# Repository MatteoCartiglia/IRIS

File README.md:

# IRIS: Interface for Real time Intelligent Systems

##  Overview

IRIS contains the necessary resources to interface custom ASICS built in the NCS group with Teensy microcontroller boards. 
IRIS enables novel chips to be prototyped and tested quickly and efficiently without having to deal with tedious interfacing.  It interfaces seamlessly different communication protocols such as I2C, SPI and custom four phase handshakes. Doing so  different building blocks can be reconfigured to meet the demands of any new chip.

The building blocks it supports are:
- DAC
- Input interface
- SPI
- BiasGenerator
- Output Encoder

## Code overview

A user friendly GUI controls the backend which runs on the teensy board. Communication between these two parts is crucial and ensures accurate transmission of all data. 

## Frontend

The frontend runs using the 'Dear ImGui' (https://github.com/ocornut/imgui) C++ interface with GLFW (http://www.glfw.org) and OpenGL (https://www.opengl.org/) backends. The relevant files of ImGui and OpenGL are included in this repository. 

## Backend

This code is compiled and uploaded using "PlatformIO" plugin on Visual Studio Code.

## Getting Started

1. Install the required dependencies (GLFW, platformIO plugin)
2. Connect the Teensy to the PC and check how it appears in the /dev directory. You can do this by running `ls /dev`. It will typically appear as `ttyACM0`, however it may also appear under another name, depending on your machine. If it does not appear as `ttyACM0`, update the `SERIAl_PORT_NAME` variable in the `teensy_backend/include/constants.h` file.
3. Upload the backend code to Teensy using the PlatformIO plugin.
4. In the `imgui_frontend` directory, run the shell script `clean_build_ruh.sh`. This will build and run an `alive_interface` executable.

Current boards that have been tested are:
- ALIVE
- SPIAC
- AHPC

## Contributors:
* Matteo Cartiglia

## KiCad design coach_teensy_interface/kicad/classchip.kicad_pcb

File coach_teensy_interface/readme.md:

## Overview

This project contains the resources necessary to use a [Teensy 4.0](https://www.pjrc.com/store/teensy40.html) to interface with the CoACH neuromorphic classchip via the PLANE board.

The `datasheets` folder contains datasheets for the chips used on the PCB.

The `kicad` folder contains the schematic and layout of the PCB.

The `src/config` folder contains a file used by CMake to provide version number macros.

The `src/pc` folder contains code to build a Python extension module (`pyplane`) through which the PLANE board and CoACH chip can be controlled from Python.

The `src/teensy` folder contains the code that needs to be uploaded to the Teensy.

The CoACH chip itself is documented in the [CoACH-docs project](https://code.ini.uzh.ch/CoACH/CoACH-docs).

## To Build the Software

### Prerequisites
* Linux, preferably Ubuntu
* Arduino software
* Teensyduino
* `teensy_loader_cli` from https://github.com/PaulStoffregen/teensy_loader_cli - see comments in [load-teensy.sh](load-teensy.sh) for detailed build and install instructions
* pybind11: https://pybind11.readthedocs.io - see https://pybind11.readthedocs.io/en/stable/installing.html#include-with-pypi for installation instructions (Hint: you probably want to use the `pip install "pybind11[global]"` method in order to get the pybind11 CMake files, but this will depend on your environment)

The Arduino software and Teensyarduino can be installed as follows:

```
cd /parent/dir/for/arduino/software
wget https://downloads.arduino.cc/arduino-1.8.13-linux64.tar.xz
wget https://www.pjrc.com/teensy/td_153/TeensyduinoInstall.linux64
tar -xf arduino-1.8.13-linux64.tar.xz
chmod +x TeensyduinoInstall.linux64
./TeensyduinoInstall.linux64 --dir=arduino-1.8.13
cd arduino-1.8.13/hardware/teensy/avr/cores/teensy4
make main.elf
```

Once you have all the prerequisites installed, you can clone this project and proceed to build it as follows.

### Command Line Build

In the `CoACH_teensy_interface` directory, do the following (replacing `/parent/dir/for/arduino/software/arduino-1.8.13` with the actual directory you installed the Arduino software in, obviously).

```
mkdir build && cd build
cmake -DARDUINOPATH=/parent/dir/for/arduino/software/arduino-1.8.13 ../src
make -j
```

The build produces
* `teensy/main.hex` which can be uploaded to the Teensy using the `load-teensy.sh` script, which in turn uses `teensy_loader_cli`.
* The Python extension module e.g. `pc/pyplane/pyplane.cpython-36m-x86_64-linux-gnu.so` which needs to be on the `PYTHONPATH` in order to be importable from Python.

### Building the Teensy Code using an IDE

An IDE can be used to take care of compiling and uploading the code to the Teensy. For Visual Studio Code, the [PlatformIO](https://platformio.org/) extension can be used for this. To do this with the Arduino IDE, follow [these](https://www.pjrc.com/teensy/td_download.html) instructions.

If Visual Studio Code is to be used, create a new project from the PlatformIO home screen. Choose Teensy 4.0 as the board and Arduino as the framework. Then copy everything in `teensy/*` to the `src/*` folder of the newly created project.

If the Arduino IDE is to be used, rename `teensy/main.cpp` to `teensy/teensy.ino`.

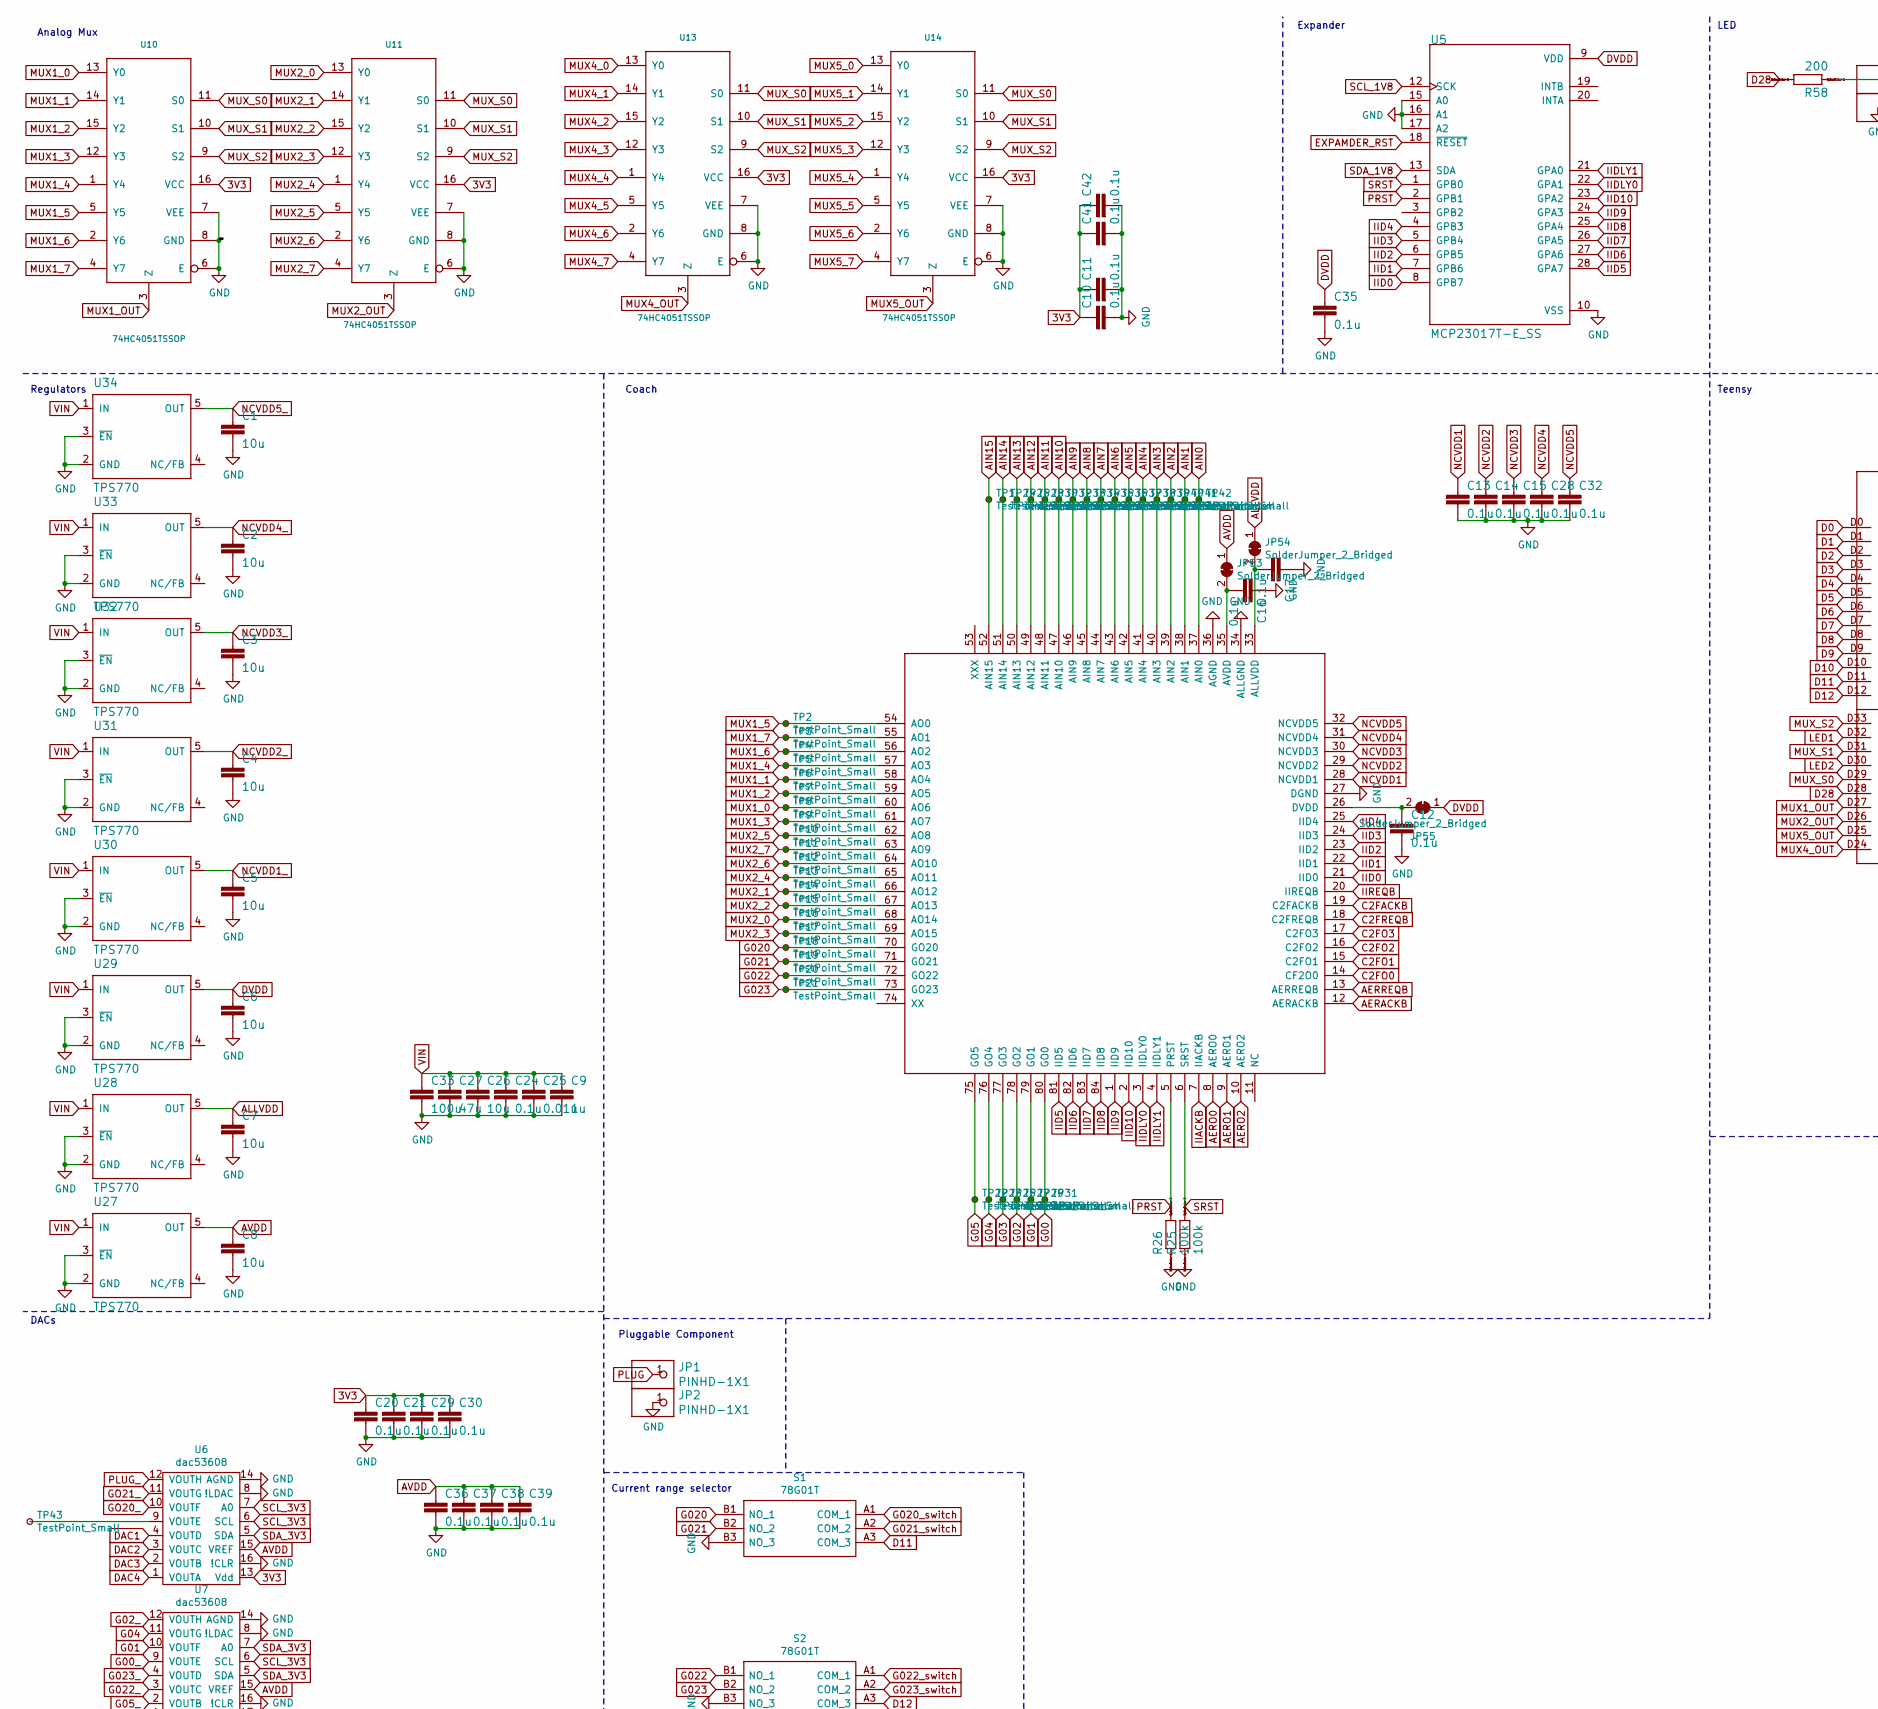
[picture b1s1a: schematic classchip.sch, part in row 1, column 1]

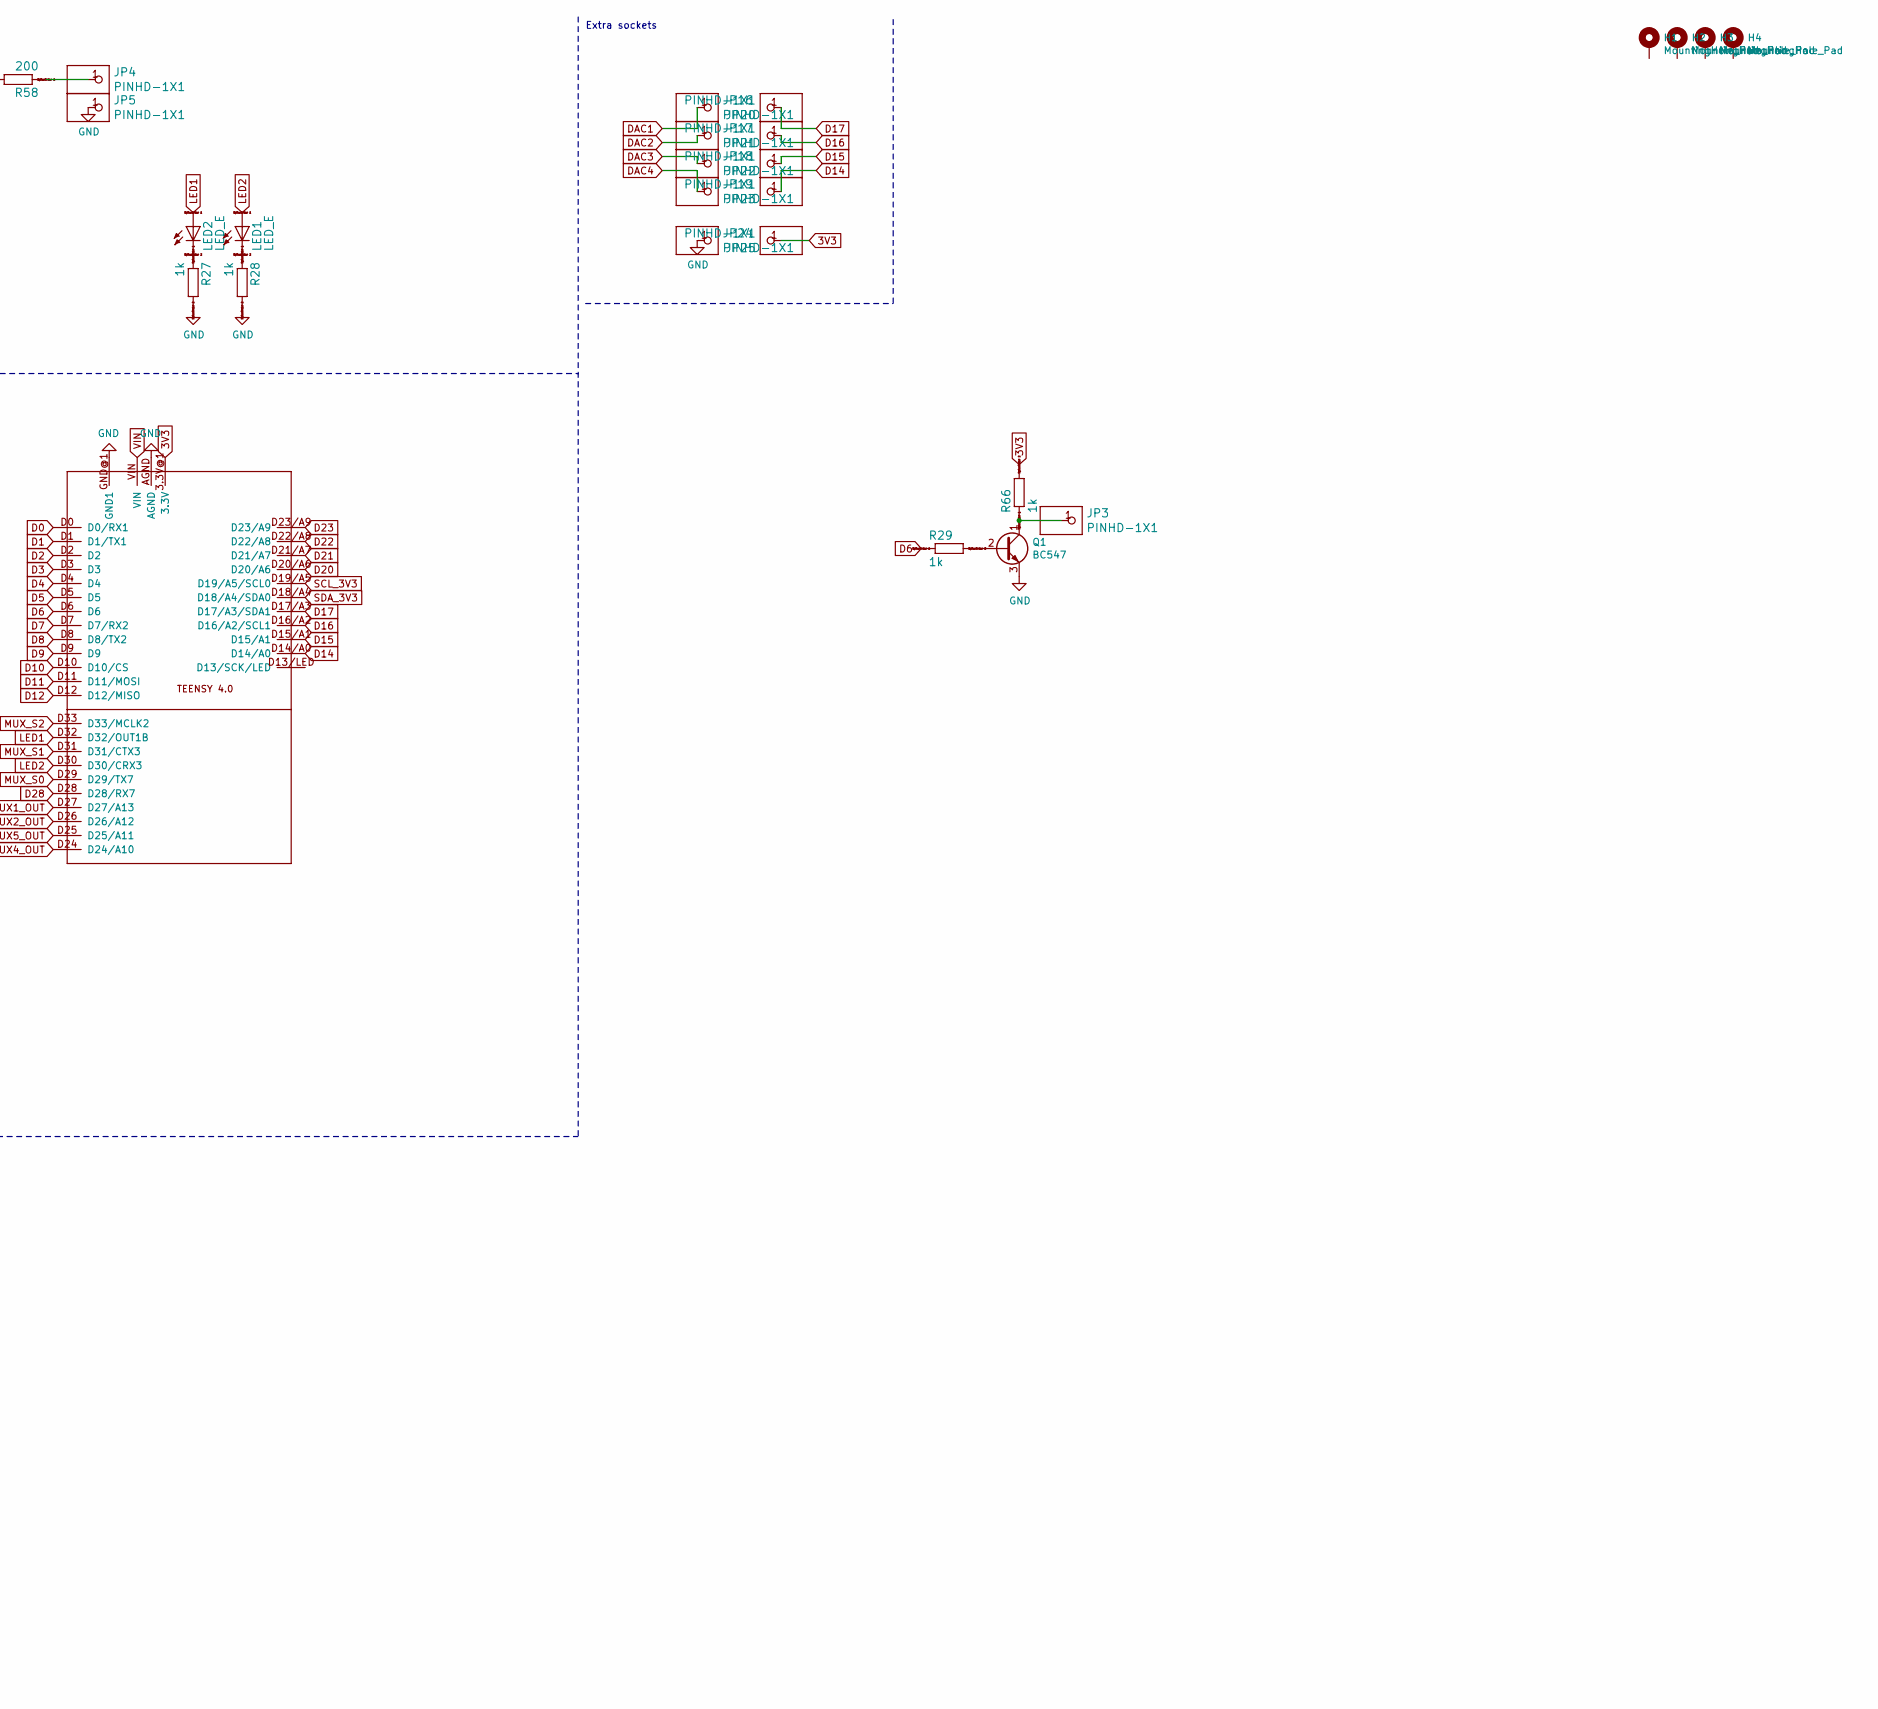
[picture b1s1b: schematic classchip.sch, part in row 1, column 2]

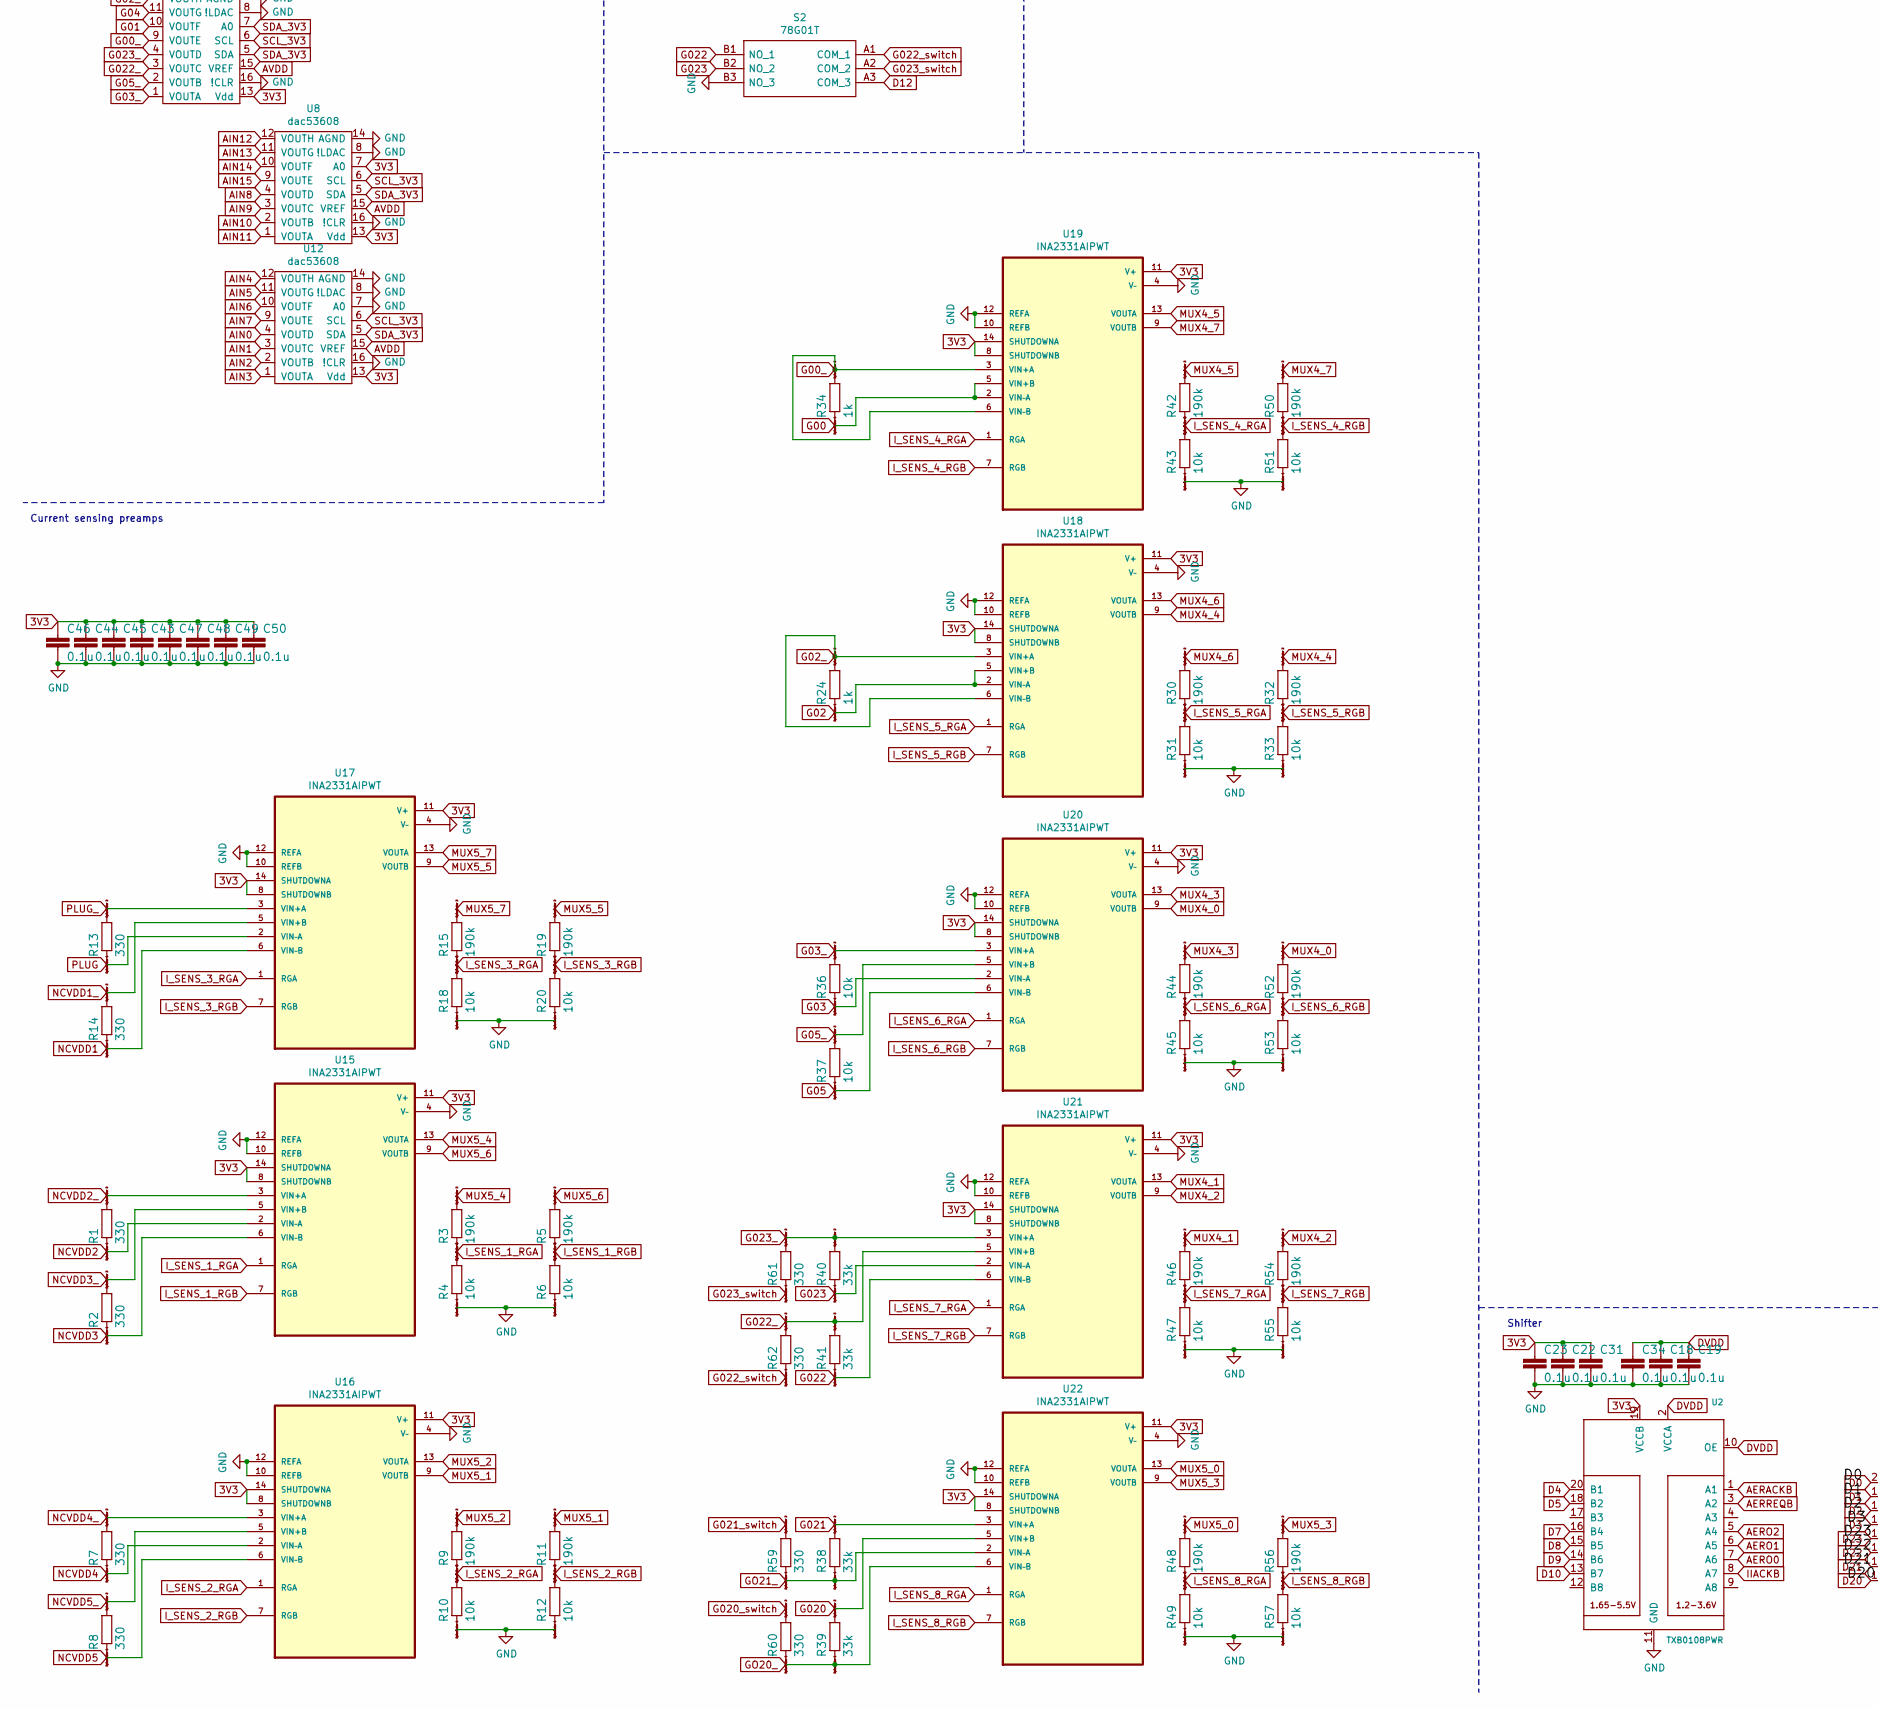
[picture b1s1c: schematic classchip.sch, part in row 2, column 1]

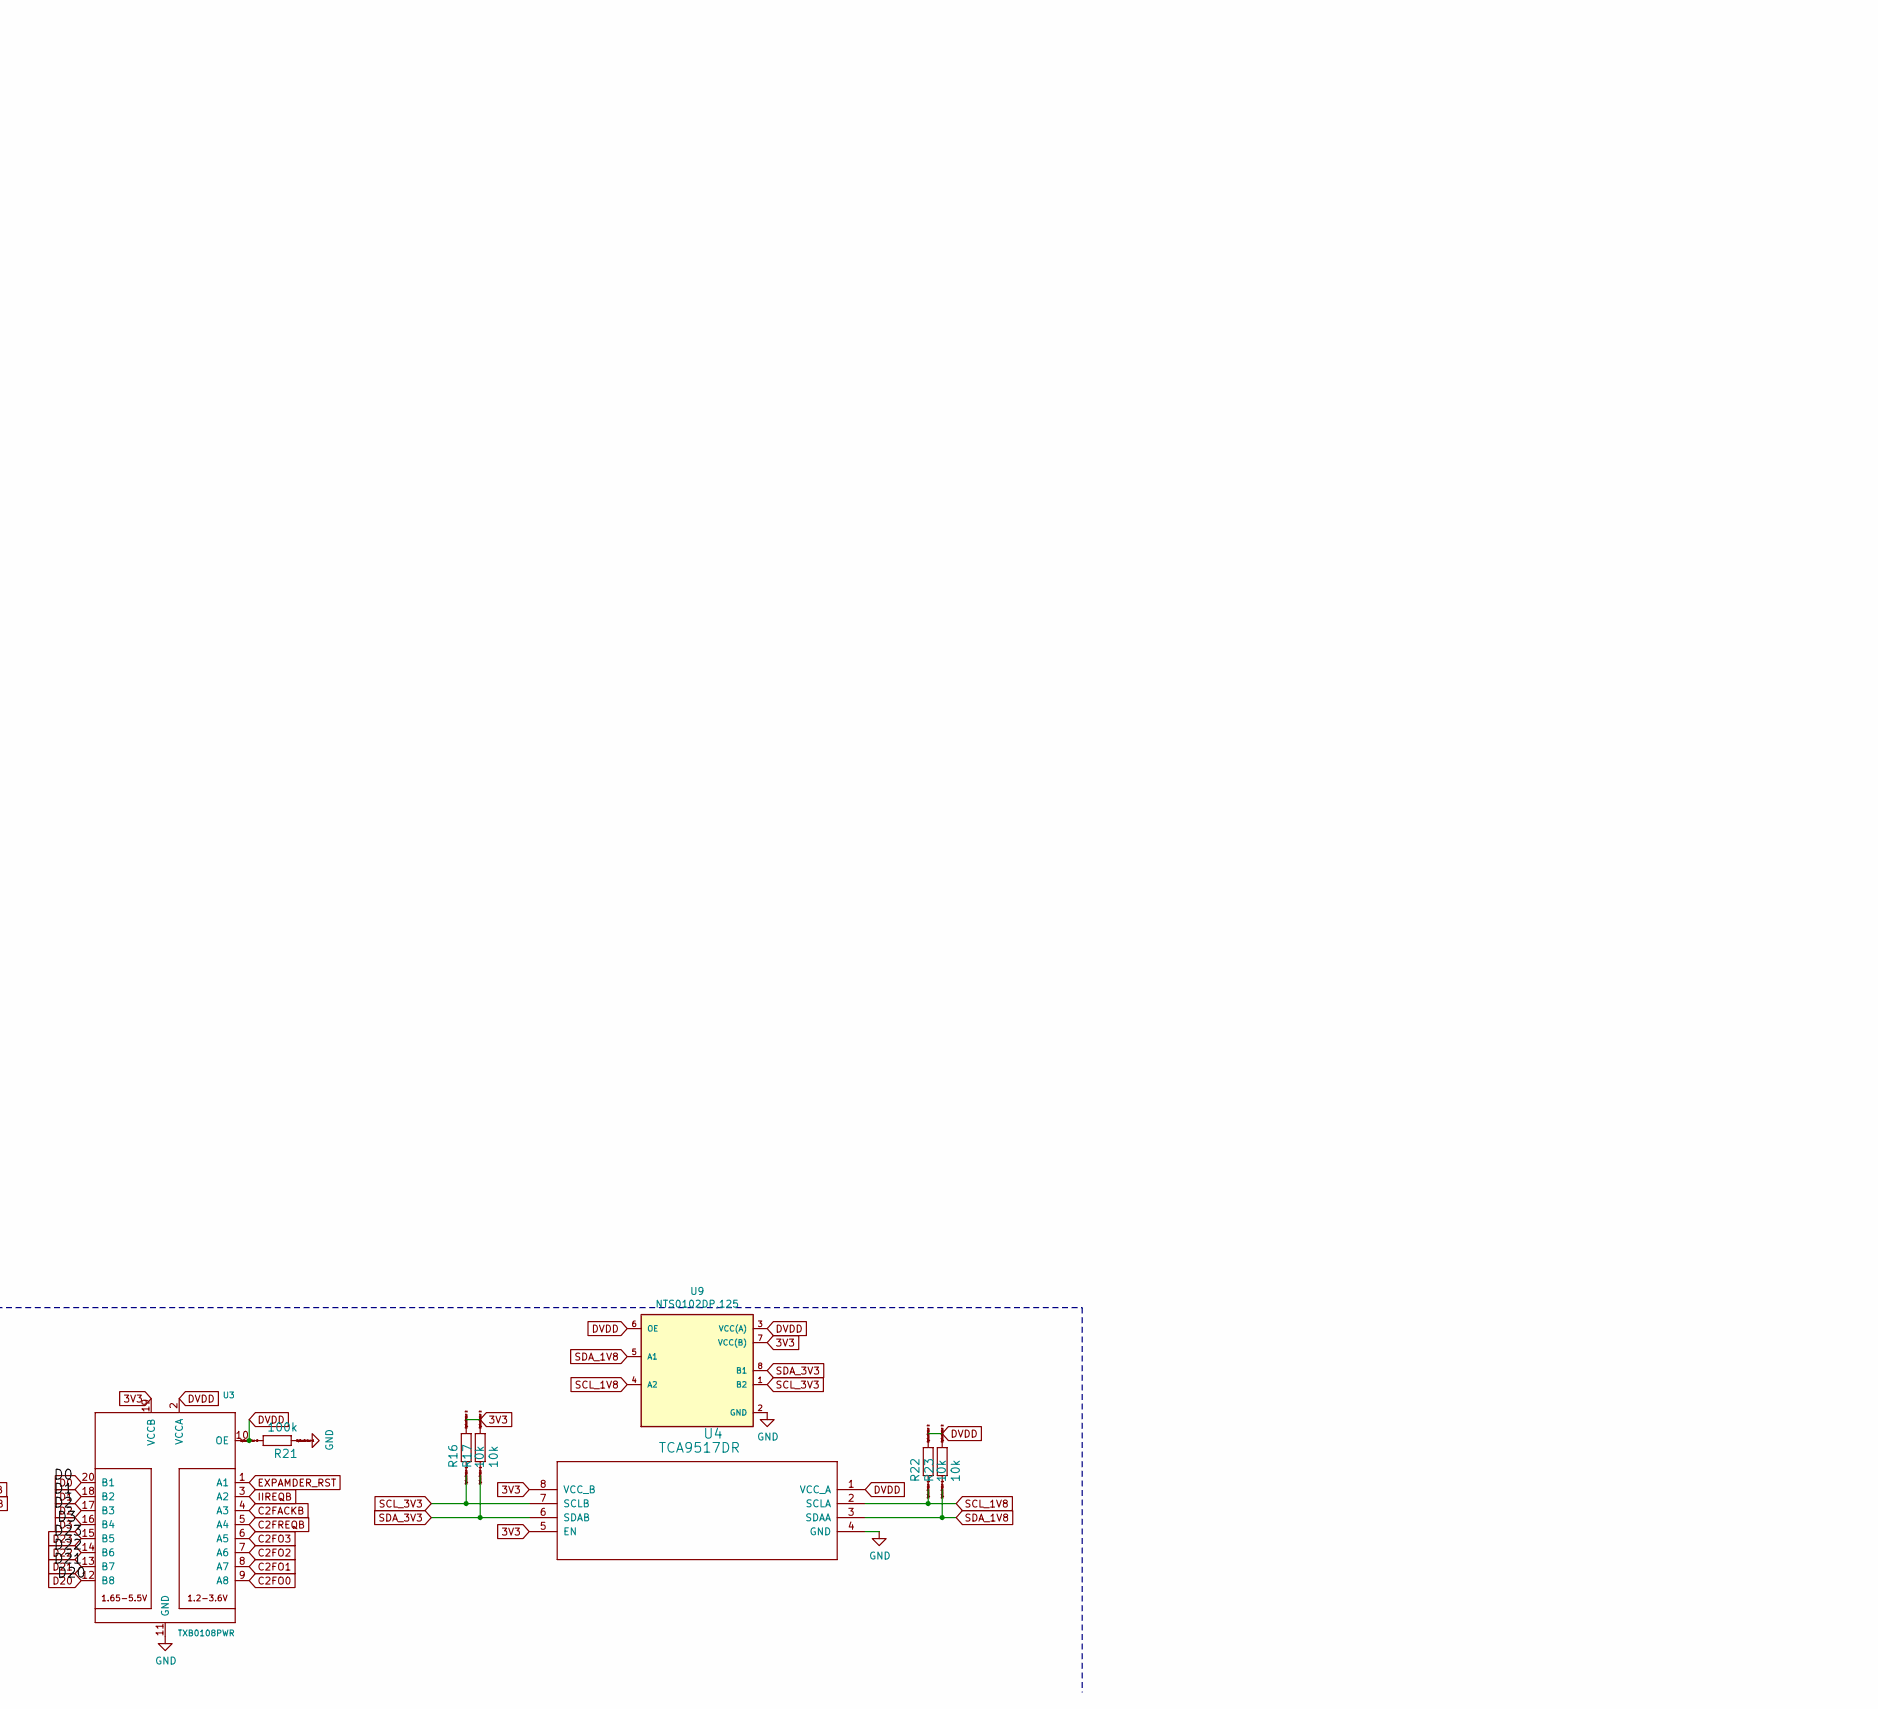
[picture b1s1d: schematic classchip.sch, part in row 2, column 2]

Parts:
C1, C2, C3, C4, C5, C6, C7, C8: 10u; C_0603_1608Metric
C9: 1u; C_0603_1608Metric
C10, C11, C12, C13, C14, C15, C16, C17, C18, C19, C20, C21, C22, C23, C28, C29, C30, C31, C32, C34, C35, C36, C37, C38, C39, C41, C42, C43, C44, C45, C46, C47, C48, C49, C50: 0.1u; C_0603_1608Metric
C24: 0.1u; C_0805_2012Metric
C25: 0.01u; C_0603_1608Metric
C26: 10u; C_1206_3216Metric
C27: 47u; C025-024X044
C33: 100u; C025-024X044
H1, H2, H3, H4: MountingHole_Pad; MountingHole_4.3mm_M4_ISO14580
JP1, JP2, JP3, JP4, JP5, JP16, JP17, JP18, JP19, JP20, JP21, JP22, JP23, JP24, JP25: PINHD-1X1; 1X01
JP53, JP54, JP55: SolderJumper_2_Bridged; SolderJumper-2_P1.3mm_Bridged_RoundedPad1.0x1.5mm
LED1, LED2: LED_E; LED_1206
Q1: BC547; TO-92_Inline
R1, R2, R7, R8, R13, R14, R59, R60, R61, R62: 330; R_0603_1608Metric
R3, R5, R9, R11, R15, R19, R30, R32, R42, R44, R46, R48, R50, R52, R54, R56: 190k; R_0603_1608Metric
R4, R6, R10, R12, R16, R17, R18, R20, R22, R23, R31, R33, R36, R37, R43, R45, R47, R49, R51, R53, R55, R57: 10k; R_0603_1608Metric
R21, R25, R26: 100k; R_0603_1608Metric
R24, R27, R28, R29, R34, R66: 1k; R_0603_1608Metric
R38, R39, R40, R41: 33k; R_0603_1608Metric
R58: 200; R_0603_1608Metric
S1, S2: 78G01T; Manufacturer_Part_Number 78G01T; Mouser Part Number 706-78G01T
TEENSY1: MY_TEENSY
TP1, TP2, TP3, TP4, TP5, TP6, TP7, TP8, TP9, TP10, TP11, TP12, TP13, TP14, TP15, TP16, TP17, TP18, TP19, TP20, TP21, TP22, TP23, TP24, TP25, TP26, TP27, TP28, TP29, TP30, TP31, TP32, TP33, TP34, TP35, TP36, TP37, TP38, TP39, TP40, TP41, TP42, TP43: TestPoint_Small; TestPoint_Pad_D1.0mm
U1: AE11110-ND; S84
U2, U3: TXB0108PWR; TSSOP20
U4: TCA9517DR; SOT96-1_NXP
U5: MCP23017T-E_SS; SOP65P780X200-28N
U6, U7, U8, U12: dac53608; QFN50P300X300X80-17N
U9: NTS0102DP,125; SOP8P65_300X400X110L40X30N
U10, U11, U13, U14: 74HC4051TSSOP; TSSOP_16
U15, U16, U17, U18, U19, U20, U21, U22: INA2331AIPWT; SOP65P640X120-14N
U27, U28, U29, U30, U31, U32, U33, U34: TPS770; SOT23-DBV

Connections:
3V3: C10.1, C11.1, C20.1, C21.1, C22.1, C23.1, C29.1, C30.1, C31.1, C41.1, C42.1, C43.1, C44.1, C45.1, C46.1, C47.1, C48.1, C49.1, C50.1, JP25.1, R16.2, R17.2, R66.2, TEENSY1.3.3V@1 (3.3V), U2.19 (VCCB), U3.19 (VCCB), U4.5 (EN), U4.8 (VCC_B), U6.13 (Vdd), U7.13 (Vdd), U8.7 (A0), U8.13 (Vdd), U9.7 (VCC(B)), U10.16 (VCC), U11.16 (VCC), U12.13 (Vdd), U13.16 (VCC), U14.16 (VCC), U15.8 (SHUTDOWNB), U15.11 (V+), U15.14 (SHUTDOWNA), U16.8 (SHUTDOWNB), U16.11 (V+), U16.14 (SHUTDOWNA), U17.8 (SHUTDOWNB), U17.11 (V+), U17.14 (SHUTDOWNA), U18.8 (SHUTDOWNB), U18.11 (V+), U18.14 (SHUTDOWNA), U19.8 (SHUTDOWNB), U19.11 (V+), U19.14 (SHUTDOWNA), U20.8 (SHUTDOWNB), U20.11 (V+), U20.14 (SHUTDOWNA), U21.8 (SHUTDOWNB), U21.11 (V+), U21.14 (SHUTDOWNA), U22.8 (SHUTDOWNB), U22.11 (V+), U22.14 (SHUTDOWNA)
AERACKB: U1.12 (AERACKB), U2.1 (A1)
AERO0: U1.8 (AERO0), U2.7 (A6)
AERO1: U1.9 (AERO1), U2.6 (A5)
AERO2: U1.10 (AERO2), U2.5 (A4)
AERREQB: U1.13 (AERREQB), U2.3 (A2)
AIN0: TP42.1, U1.37 (AIN0), U12.4 (VOUTD)
AIN1: TP41.1, U1.38 (AIN1), U12.3 (VOUTC)
AIN2: TP40.1, U1.39 (AIN2), U12.2 (VOUTB)
AIN3: TP39.1, U1.40 (AIN3), U12.1 (VOUTA)
AIN4: TP38.1, U1.41 (AIN4), U12.12 (VOUTH)
AIN5: TP37.1, U1.42 (AIN5), U12.11 (VOUTG)
AIN6: TP36.1, U1.43 (AIN6), U12.10 (VOUTF)
AIN7: TP35.1, U1.44 (AIN7), U12.9 (VOUTE)
AIN8: TP34.1, U1.45 (AIN8), U8.4 (VOUTD)
AIN9: TP33.1, U1.46 (AIN9), U8.3 (VOUTC)
AIN10: TP32.1, U1.47 (AIN10), U8.2 (VOUTB)
AIN11: TP30.1, U1.48 (AIN11), U8.1 (VOUTA)
AIN12: TP28.1, U1.49 (AIN12), U8.12 (VOUTH)
AIN13: TP26.1, U1.50 (AIN13), U8.11 (VOUTG)
AIN14: TP24.1, U1.51 (AIN14), U8.10 (VOUTF)
AIN15: TP1.1, U1.52 (AIN15), U8.9 (VOUTE)
ALLVDD: C7.1, JP54.1 (A), U28.5 (OUT)
AVDD: C8.1, C36.1, C37.1, C38.1, C39.1, JP53.1 (A), U6.15 (VREF), U7.15 (VREF), U8.15 (VREF), U12.15 (VREF), U27.5 (OUT)
C2FACKB: U1.19 (C2FACKB), U3.4 (A3)
C2FO0: U1.14 (CF2O0), U3.9 (A8)
C2FO1: U1.15 (C2FO1), U3.8 (A7)
C2FO2: U1.16 (C2FO2), U3.7 (A6)
C2FO3: U1.17 (C2FO3), U3.6 (A5)
C2FREQB: U1.18 (C2FREQB), U3.5 (A4)
D0: TEENSY1.D0 (D0/RX1), U3.20 (B1)
D1: TEENSY1.D1 (D1/TX1), U3.18 (B2)
D2: TEENSY1.D2, U3.17 (B3)
D3: TEENSY1.D3, U3.16 (B4)
D4: TEENSY1.D4, U2.20 (B1)
D5: TEENSY1.D5, U2.18 (B2)
D6: R29.1, TEENSY1.D6
D7: TEENSY1.D7 (D7/RX2), U2.16 (B4)
D8: TEENSY1.D8 (D8/TX2), U2.15 (B5)
D9: TEENSY1.D9, U2.14 (B6)
D10: TEENSY1.D10 (D10/CS), U2.13 (B7)
D11: S1.A3 (COM_3), TEENSY1.D11 (D11/MOSI)
D12: S2.A3 (COM_3), TEENSY1.D12 (D12/MISO)
D14: JP23.1, TEENSY1.D14/A0
D15: JP22.1, TEENSY1.D15/A1
D16: JP21.1, TEENSY1.D16/A2 (D16/A2/SCL1)
D17: JP20.1, TEENSY1.D17/A3 (D17/A3/SDA1)
D20: TEENSY1.D20/A6, U3.12 (B8)
D21: TEENSY1.D21/A7, U3.13 (B7)
D22: TEENSY1.D22/A8, U3.14 (B6)
D23: TEENSY1.D23/A9, U3.15 (B5)
D28: R58.2, TEENSY1.D28 (D28/RX7)
DAC1: JP16.1, U6.4 (VOUTD)
DAC2: JP17.1, U6.3 (VOUTC)
DAC3: JP18.1, U6.2 (VOUTB)
DAC4: JP19.1, U6.1 (VOUTA)
DVDD: C6.1, C18.1, C19.1, C34.1, C35.1, JP55.1 (A), R21.2, R22.2, R23.2, U2.2 (VCCA), U2.10 (OE), U3.2 (VCCA), U3.10 (OE), U4.1 (VCC_A), U5.9 (VDD), U9.3 (VCC(A)), U9.6 (OE), U29.5 (OUT)
EXPAMDER_RST: U3.1 (A1), U5.18 (~RESET)
G00: R34.1, TP31.1, U1.80 (GO0), U19.2 (VIN–A), U19.5 (VIN+B)
G00_: R34.2, U7.9 (VOUTE), U19.3 (VIN+A), U19.6 (VIN–B)
G01: TP29.1, U1.79 (GO1), U7.10 (VOUTF)
G02: R24.1, TP27.1, U1.78 (GO2), U18.2 (VIN–A), U18.5 (VIN+B)
G02_: R24.2, U7.12 (VOUTH), U18.3 (VIN+A), U18.6 (VIN–B)
G03: R36.1, TP25.1, U1.77 (GO3), U20.2 (VIN–A)
G03_: R36.2, U7.1 (VOUTA), U20.3 (VIN+A)
G04: TP23.1, U1.76 (GO4), U7.11 (VOUTG)
G05: R37.1, TP22.1, U1.75 (GO5), U20.6 (VIN–B)
G05_: R37.2, U7.2 (VOUTB), U20.5 (VIN+B)
G020: R39.2, S1.B1 (NO_1), TP18.1, U1.70 (GO20), U22.5 (VIN+B)
G020_switch: R60.2, S1.A1 (COM_1)
G021: R38.2, S1.B2 (NO_2), TP19.1, U1.71 (GO21), U22.3 (VIN+A)
G021_switch: R59.2, S1.A2 (COM_2)
G022: R41.1, S2.B1 (NO_1), TP20.1, U1.72 (GO22), U21.6 (VIN–B)
G022_: R41.2, R62.2, U7.3 (VOUTC), U21.5 (VIN+B)
G022_switch: R62.1, S2.A1 (COM_1)
G023: R40.1, S2.B2 (NO_2), TP21.1, U1.73 (GO23), U21.2 (VIN–A)
G023_: R40.2, R61.2, U7.4 (VOUTD), U21.3 (VIN+A)
G023_switch: R61.1, S2.A2 (COM_2)
GND: C1.2, C2.2, C3.2, C4.2, C5.2, C6.2, C7.2, C8.2, C9.2, C10.2, C11.2, C12.2, C13.2, C14.2, C15.2, C16.1, C17.1, C18.2, C19.2, C20.2, C21.2, C22.2, C23.2, C24.2, C25.2, C26.2, C27.2, C28.2, C29.2, C30.2, C31.2, C32.2, C33.2, C34.2, C35.2, C36.2, C37.2, C38.2, C39.2, C41.2, C42.2, C43.2, C44.2, C45.2, C46.2, C47.2, C48.2, C49.2, C50.2, JP2.1, JP5.1, JP24.1, Q1.3 (E), R4.1, R6.1, R10.1, R12.1, R18.1, R20.1, R21.1, R25.1, R26.1, R27.2, R28.2, R31.1, R33.1, R43.1, R45.1, R47.1, R49.1, R51.1, R53.1, R55.1, R57.1, S1.B3 (NO_3), S2.B3 (NO_3), TEENSY1.AGND, TEENSY1.GND@1 (GND1), U1.27 (DGND), U1.34 (ALLGND), U1.36 (AGND), U2.11 (GND), U3.11 (GND), U4.4 (GND), U5.10 (VSS), U5.15 (A0), U5.16 (A1), U5.17 (A2), U6.8 (!LDAC), U6.14 (AGND), U6.16 (!CLR)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
GO20_: R39.1, R60.1, U6.10 (VOUTF), U22.6 (VIN–B)
GO21_: R38.1, R59.1, U6.11 (VOUTG), U22.2 (VIN–A)
IIACKB: U1.7 (IIACKB), U2.8 (A7)
IID0: U1.21 (IID0), U5.8 (GPB7)
IID1: U1.22 (IID1), U5.7 (GPB6)
IID2: U1.23 (IID2), U5.6 (GPB5)
IID3: U1.24 (IID3), U5.5 (GPB4)
IID4: U1.25 (IID4), U5.4 (GPB3)
IID5: U1.81 (IID5), U5.28 (GPA7)
IID6: U1.82 (IID6), U5.27 (GPA6)
IID7: U1.83 (IID7), U5.26 (GPA5)
IID8: U1.84 (IID8), U5.25 (GPA4)
IID9: U1.1 (IID9), U5.24 (GPA3)
IID10: U1.2 (IID10), U5.23 (GPA2)
IIDLY0: U1.3 (IIDLY0), U5.22 (GPA1)
IIDLY1: U1.4 (IIDLY1), U5.21 (GPA0)
IIREQB: U1.20 (IIREQB), U3.3 (A2)
I_SENS_1_RGA: R3.1, R4.2, U15.1 (RGA)
I_SENS_1_RGB: R5.1, R6.2, U15.7 (RGB)
I_SENS_2_RGA: R9.1, R10.2, U16.1 (RGA)
I_SENS_2_RGB: R11.1, R12.2, U16.7 (RGB)
I_SENS_3_RGA: R15.1, R18.2, U17.1 (RGA)
I_SENS_3_RGB: R19.1, R20.2, U17.7 (RGB)
I_SENS_4_RGA: R42.1, R43.2, U19.1 (RGA)
I_SENS_4_RGB: R50.1, R51.2, U19.7 (RGB)
I_SENS_5_RGA: R30.1, R31.2, U18.1 (RGA)
I_SENS_5_RGB: R32.1, R33.2, U18.7 (RGB)
I_SENS_6_RGA: R44.1, R45.2, U20.1 (RGA)
I_SENS_6_RGB: R52.1, R53.2, U20.7 (RGB)
I_SENS_7_RGA: R46.1, R47.2, U21.1 (RGA)
I_SENS_7_RGB: R54.1, R55.2, U21.7 (RGB)
I_SENS_8_RGA: R48.1, R49.2, U22.1 (RGA)
I_SENS_8_RGB: R56.1, R57.2, U22.7 (RGB)
LED1: LED2.A, TEENSY1.D32 (D32/OUT1B)
LED2: LED1.A, TEENSY1.D30 (D30/CRX3)
MUX1_0: TP8.1, U1.60 (AO6), U10.13 (Y0)
MUX1_1: TP6.1, U1.58 (AO4), U10.14 (Y1)
MUX1_2: TP7.1, U1.59 (AO5), U10.15 (Y2)
MUX1_3: TP9.1, U1.61 (AO7), U10.12 (Y3)
MUX1_4: TP5.1, U1.57 (AO3), U10.1 (Y4)
MUX1_5: TP2.1, U1.54 (AO0), U10.5 (Y5)
MUX1_6: TP4.1, U1.56 (AO2), U10.2 (Y6)
MUX1_7: TP3.1, U1.55 (AO1), U10.4 (Y7)
MUX1_OUT: TEENSY1.D27 (D27/A13), U10.3 (Z)
MUX2_0: TP16.1, U1.68 (AO14), U11.13 (Y0)
MUX2_1: TP14.1, U1.66 (AO12), U11.14 (Y1)
MUX2_2: TP15.1, U1.67 (AO13), U11.15 (Y2)
MUX2_3: TP17.1, U1.69 (AO15), U11.12 (Y3)
MUX2_4: TP13.1, U1.65 (AO11), U11.1 (Y4)
MUX2_5: TP10.1, U1.62 (AO8), U11.5 (Y5)
MUX2_6: TP12.1, U1.64 (AO10), U11.2 (Y6)
MUX2_7: TP11.1, U1.63 (AO9), U11.4 (Y7)
MUX2_OUT: TEENSY1.D26 (D26/A12), U11.3 (Z)
MUX4_0: R52.2, U13.13 (Y0), U20.9 (VOUTB)
MUX4_1: R46.2, U13.14 (Y1), U21.13 (VOUTA)
MUX4_2: R54.2, U13.15 (Y2), U21.9 (VOUTB)
MUX4_3: R44.2, U13.12 (Y3), U20.13 (VOUTA)
MUX4_4: R32.2, U13.1 (Y4), U18.9 (VOUTB)
MUX4_5: R42.2, U13.5 (Y5), U19.13 (VOUTA)
MUX4_6: R30.2, U13.2 (Y6), U18.13 (VOUTA)
MUX4_7: R50.2, U13.4 (Y7), U19.9 (VOUTB)
MUX4_OUT: TEENSY1.D24 (D24/A10), U13.3 (Z)
MUX5_0: R48.2, U14.13 (Y0), U22.13 (VOUTA)
MUX5_1: R11.2, U14.14 (Y1), U16.9 (VOUTB)
MUX5_2: R9.2, U14.15 (Y2), U16.13 (VOUTA)
MUX5_3: R56.2, U14.12 (Y3), U22.9 (VOUTB)
MUX5_4: R3.2, U14.1 (Y4), U15.13 (VOUTA)
MUX5_5: R19.2, U14.5 (Y5), U17.9 (VOUTB)
MUX5_6: R5.2, U14.2 (Y6), U15.9 (VOUTB)
MUX5_7: R15.2, U14.4 (Y7), U17.13 (VOUTA)
MUX5_OUT: TEENSY1.D25 (D25/A11), U14.3 (Z)
MUX_S0: TEENSY1.D29 (D29/TX7), U10.11 (S0), U11.11 (S0), U13.11 (S0), U14.11 (S0)
MUX_S1: TEENSY1.D31 (D31/CTX3), U10.10 (S1), U11.10 (S1), U13.10 (S1), U14.10 (S1)
MUX_S2: TEENSY1.D33 (D33/MCLK2), U10.9 (S2), U11.9 (S2), U13.9 (S2), U14.9 (S2)
NCVDD1: C13.1, R14.1, U1.28 (NCVDD1), U17.6 (VIN–B)
NCVDD1_: C5.1, R14.2, U17.5 (VIN+B), U30.5 (OUT)
NCVDD2: C14.1, R1.1, U1.29 (NCVDD2), U15.2 (VIN–A)
NCVDD2_: C4.1, R1.2, U15.3 (VIN+A), U31.5 (OUT)
NCVDD3: C15.1, R2.1, U1.30 (NCVDD3), U15.6 (VIN–B)
NCVDD3_: C3.1, R2.2, U15.5 (VIN+B), U32.5 (OUT)
NCVDD4: C28.1, R7.1, U1.31 (NCVDD4), U16.2 (VIN–A)
NCVDD4_: C2.1, R7.2, U16.3 (VIN+A), U33.5 (OUT)
NCVDD5: C32.1, R8.1, U1.32 (NCVDD5), U16.6 (VIN–B)
NCVDD5_: C1.1, R8.2, U16.5 (VIN+B), U34.5 (OUT)
unnamed: C12.1, JP55.2 (B), U1.26 (DVDD)
unnamed: C16.2, JP53.2 (B), U1.35 (AVDD)
unnamed: C17.2, JP54.2 (B), U1.33 (ALLVDD)
unnamed: JP3.1, Q1.1 (C), R66.1
unnamed: JP4.1, R58.1
unnamed: LED1.C, R28.1
unnamed: LED2.C, R27.1
unnamed: Q1.2 (B), R29.2
unnamed: TP43.1, U6.9 (VOUTE)
PLUG: JP1.1, R13.1, U17.2 (VIN–A)
PLUG_: R13.2, U6.12 (VOUTH), U17.3 (VIN+A)
PRST: R26.2, U1.5 (PRST), U5.2 (GPB1)
SCL_1V8: R22.1, U4.2 (SCLA), U5.12 (SCK), U9.4 (A2)
SCL_3V3: R16.1, TEENSY1.D19/A5 (D19/A5/SCL0), U4.7 (SCLB), U6.6 (SCL), U6.7 (A0), U7.6 (SCL), U8.6 (SCL), U9.1 (B2), U12.6 (SCL)
SDA_1V8: R23.1, U4.3 (SDAA), U5.13 (SDA), U9.5 (A1)
SDA_3V3: R17.1, TEENSY1.D18/A4 (D18/A4/SDA0), U4.6 (SDAB), U6.5 (SDA), U7.5 (SDA), U7.7 (A0), U8.5 (SDA), U9.8 (B1), U12.5 (SDA)
SRST: R25.2, U1.6 (SRST), U5.1 (GPB0)
VIN: C9.1, C24.1, C25.1, C26.1, C27.1, C33.1, TEENSY1.VIN, U27.1 (IN), U28.1 (IN), U29.1 (IN), U30.1 (IN), U31.1 (IN), U32.1 (IN), U33.1 (IN), U34.1 (IN)

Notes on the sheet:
Analog Mux
Regulators
Shifter
Expander
Coach
Teensy
Current sensing preamps
LED
Pluggable Component
DACs
Extra sockets
Current range selector

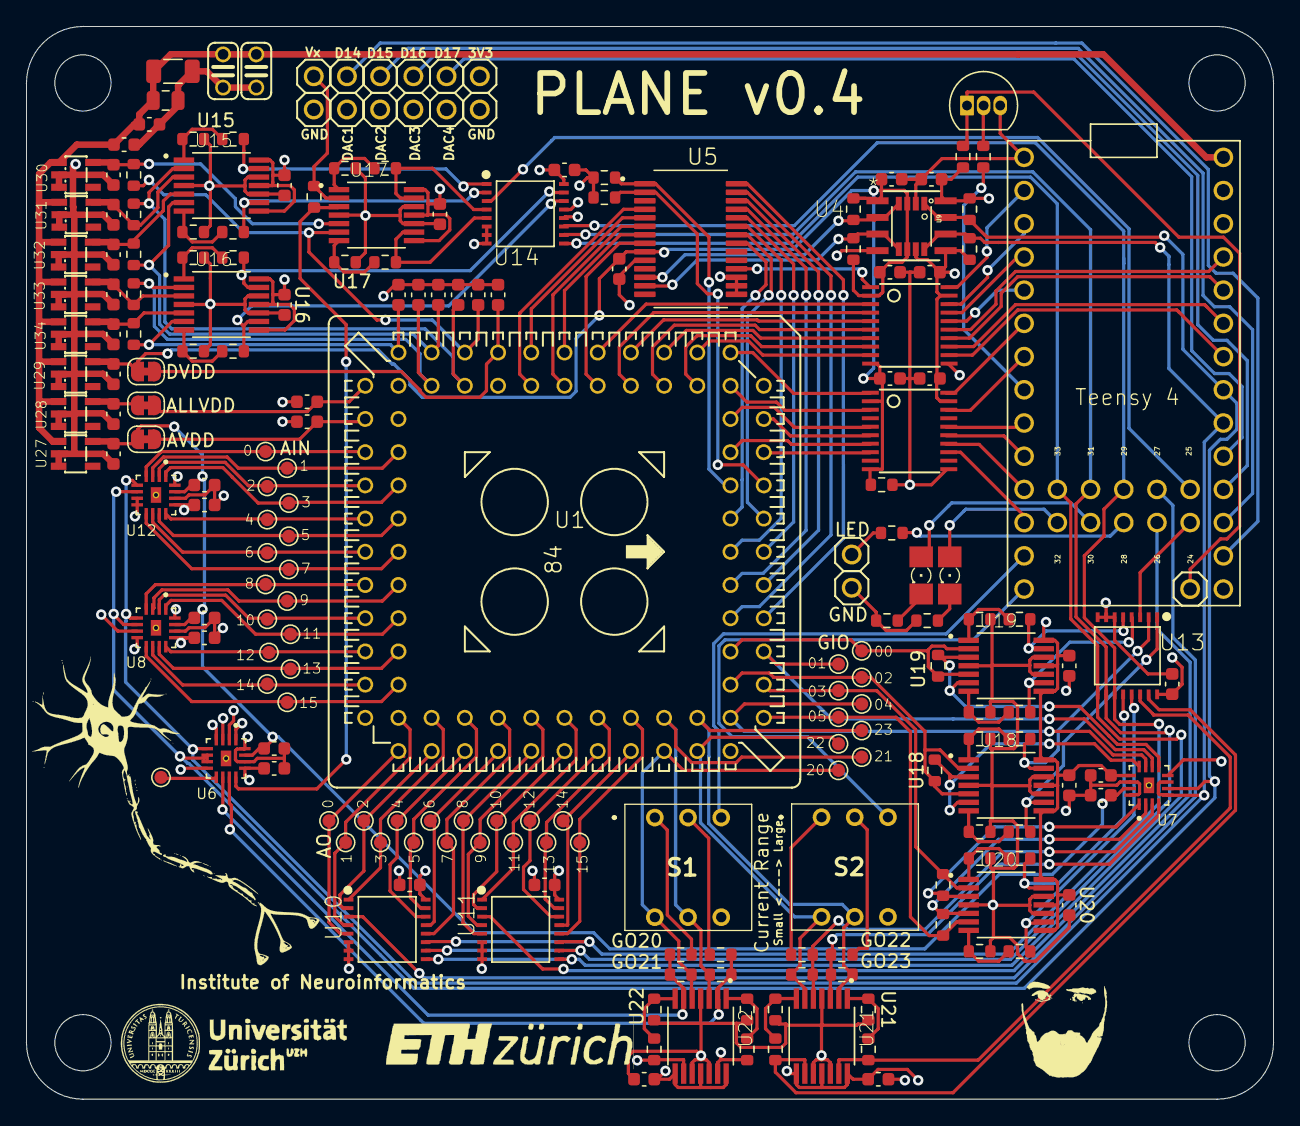
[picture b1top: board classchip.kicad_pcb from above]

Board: 4 copper layers, 95.4 x 82.0 mm, 212 parts (0 on the bottom side), 181 nets.

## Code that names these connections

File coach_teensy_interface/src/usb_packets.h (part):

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
static constexpr unsigned int NUM_DACS = 32;
enum class DacChannel {
    AIN0  = 0,
    AIN1  = 1,
    AIN2  = 2,
    AIN3  = 3,
    AIN4  = 4,
    AIN5  = 5,
    AIN6  = 6,
    AIN7  = 7,
    AIN8  = 8,
    AIN9  = 9,
    AIN10 = 10,
    AIN11 = 11,
    AIN12 = 12,
    AIN13 = 13,
    AIN14 = 14,
    AIN15 = 15,
    GO23  = 16,
    GO22  = 17,
    GO5   = 18,
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    DAC2  = 25,
    DAC3  = 26,
    DAC4  = 27,
    PLUG  = 28,
    GO21  = 29,
    GO20  = 30,
    TP    = 31
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    GO22   = 21, // Current
    GO5    = 22, // Current
    GO3    = 23, // Current
    NCVDD1 = 24, // Current
    PLUG   = 25, // Current
    NCVDD3 = 26, // Current
    NCVDD2 = 27, // Current
    NCVDD5 = 28, // Current
    NCVDD4 = 29, // Current
    GO21_N = 30, // Current
    GO20_N = 31 // Current
};
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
